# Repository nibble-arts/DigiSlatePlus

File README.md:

# DigiSlate+

The project is in an early developement state.

DigiSlate+ is inspired from the [DigiSlate](https://www.youtube.com/watch?v=TnaWQZtmPek) and the DIY timecode generator from [mitkunz](https://github.com/mitkunz/diy_timecode_generator). The aim for the DigiSlate+ is not only to be able to read and display timecode, but also to generate it itself. To make this possible, the hardware is extended by a real time clock with high running accuracy. The RTC module DS3231 with temperature-compensated quartz offers the possibility.

The DigiSlate+ has two operating states. If an external time code is fed in and the slate is switched on, it starts in read mode. The time code is read, shown on the LED display and the time in the RTC is updated. The DS3231 sends an interrupt to the controller at the beginning of each second. The offset of frames to the time code fed in is stored in the EEPROM memory in order to provide a frame-accurate time in free-running mode.

As soon as the external time code is disconnected or the slate is switched on without a time code at the input, it changes to free-running mode. It now runs automatically with the time from the RTC and the saved frame offset. The accuracy of the RTC module allows a deviation of 1 frame in 8 hours.

A socond row of 7-segment LEDs display the scene and take numbers.

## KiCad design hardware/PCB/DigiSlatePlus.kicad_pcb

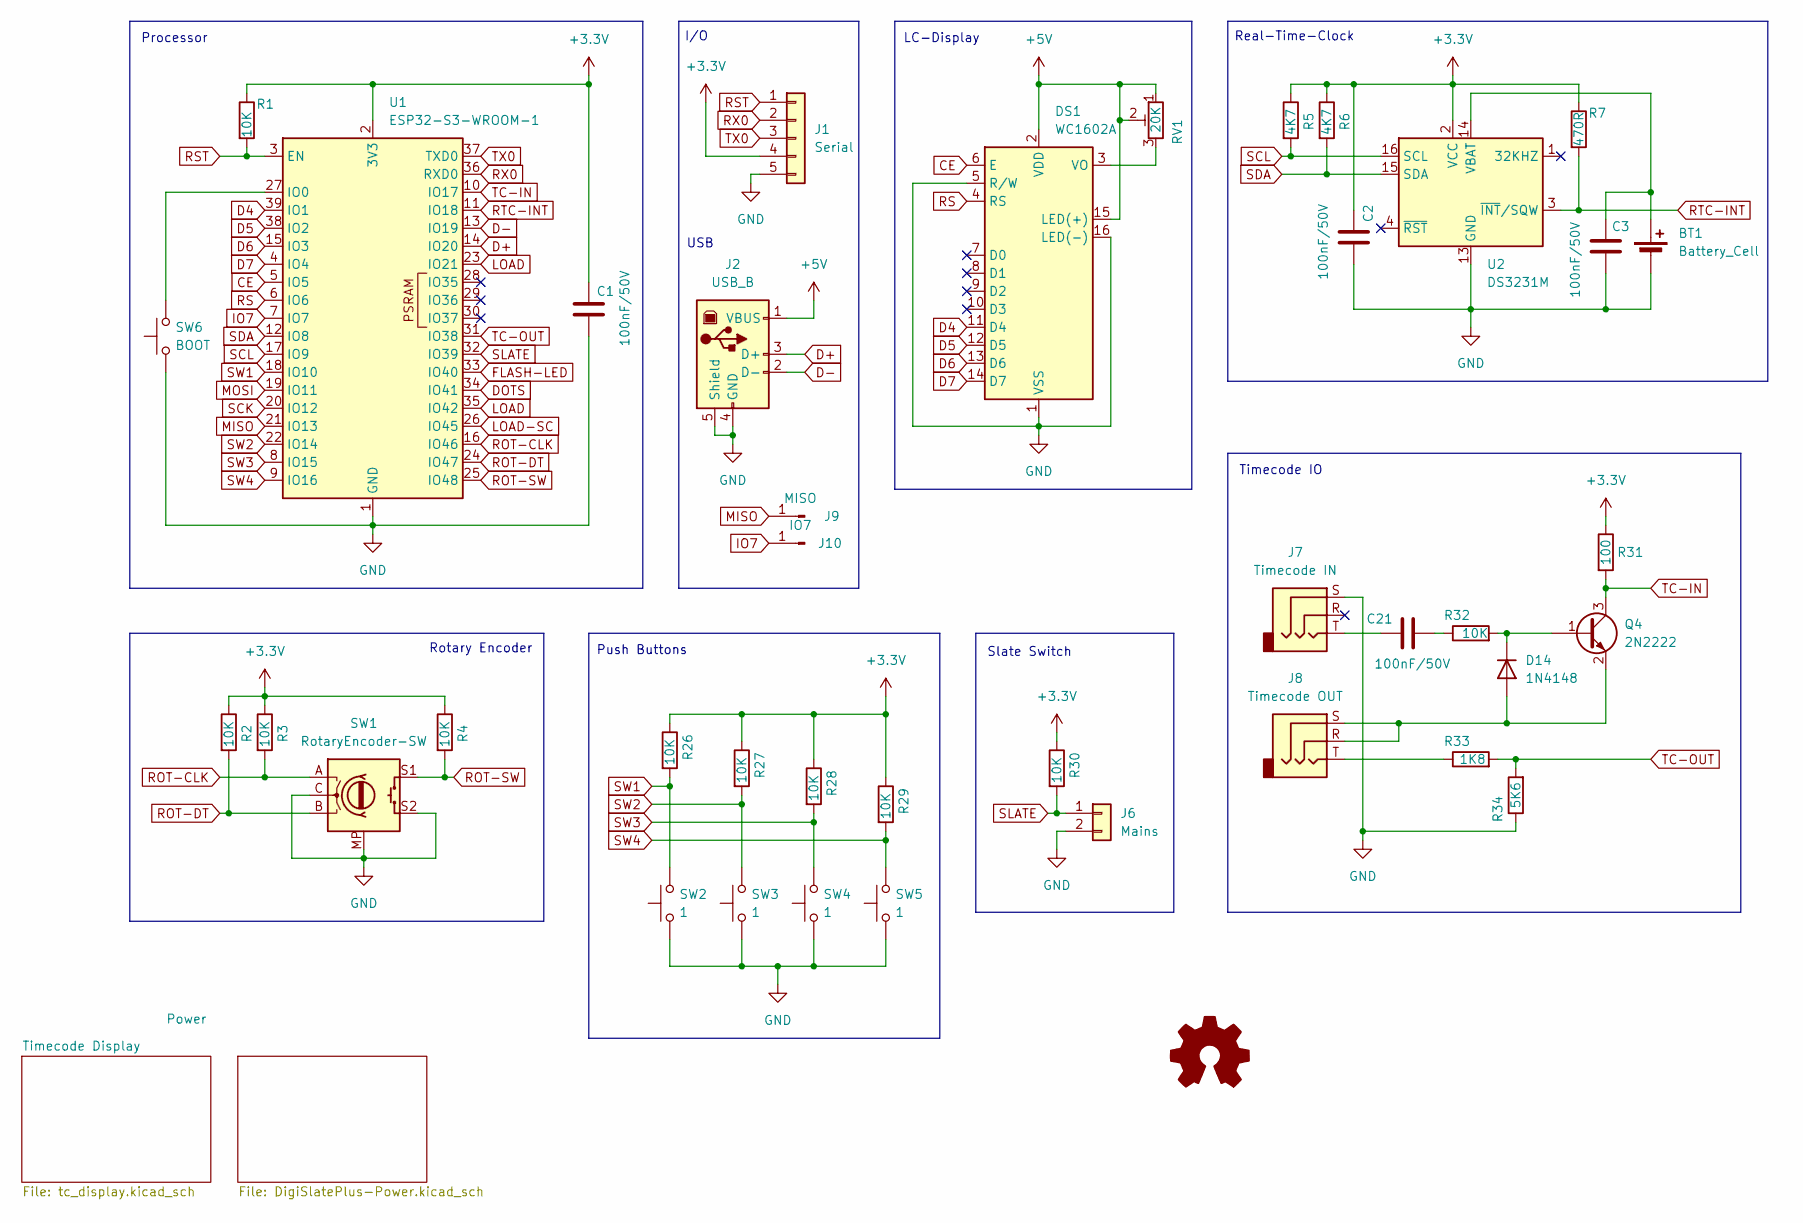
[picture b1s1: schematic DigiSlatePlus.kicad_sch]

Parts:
BT1: Battery_Cell; BatteryHolder_ComfortableElectronic_CH273-2450_1x2450
C1, C2, C3, C21: 100nF/50V; C_1206_3216Metric_Pad1.33x1.80mm_HandSolder
D14: 1N4148; D_PowerDI-123
DS1: WC1602A
J1: Serial; JST_XH_B5B-XH-AM_1x05_P2.50mm_Vertical
J2: USB_B; USB_B_Lumberg_2411_02_Horizontal
J6: Mains; JST_XH_B2B-XH-AM_1x02_P2.50mm_Vertical
J7: Timecode IN; Jack_3.5mm_CUI_SJ1-3525N_Horizontal
J8: Timecode OUT; Jack_3.5mm_CUI_SJ1-3525N_Horizontal
J9: MISO; PinHeader_1x01_P1.00mm_Vertical
J10: IO7; PinHeader_1x01_P1.00mm_Vertical
Q4: 2N2222; SOT-23
R1, R2, R3, R4, R26, R27, R28, R29, R30, R32: 10K; R_1206_3216Metric
R5, R6: 4K7; R_1206_3216Metric
R7: 470R; R_1206_3216Metric
R31: 100; R_1206_3216Metric
R33: 1K8; R_1206_3216Metric
R34: 5K6; R_1206_3216Metric
RV1: 20K; Potentiometer_Vishay_TS53YL_Vertical
SW1: RotaryEncoder-SW; RotaryEncoder_Bourns_Horizontal_PEC12R-2x17F-Sxxxx
SW2, SW3, SW4, SW5: 1; SW_PUSH-12mm
SW6: BOOT; SW_Push_SPST_NO_Alps_SKRK
U1: ESP32-S3-WROOM-1
U2: DS3231M; SOIC-16W_7.5x10.3mm_P1.27mm

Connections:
+3.3V: C1.1, C2.1, J1.4, R1.1, R2.1, R3.1, R4.1, R5.1, R6.1, R7.1, R26.1, R27.1, R28.1, R29.1, R30.1, R31.1, U1.2 (3V3), U2.2 (VCC); also elsewhere on the board
+5V: DS1.2 (VDD), DS1.15 (LED(+)), J2.1 (VBUS), RV1.1, RV1.2; also elsewhere on the board
CE: DS1.6 (E), U1.5 (IO5)
D4: DS1.11 (D4), U1.39 (IO1)
D5: DS1.12 (D5), U1.38 (IO2)
D6: DS1.13 (D6), U1.15 (IO3)
D7: DS1.14 (D7), U1.4 (IO4)
D+: J2.3 (D+), U1.14 (IO20)
D-: J2.2 (D-), U1.13 (IO19)
DOTS: U1.34 (IO41); also elsewhere on the board
FLASH-LED: U1.33 (IO40); also elsewhere on the board
GND: BT1.2 (-), C1.2, C2.2, C3.2, DS1.1 (VSS), DS1.5 (R/W), DS1.16 (LED(-)), J1.5, J2.4 (GND), J2.5 (Shield), J6.2, J7.S, R34.1, SW1.C, SW1.MP, SW1.S2, SW2.1, SW3.1, SW4.1, SW5.1, SW6.1, U1.1 (GND), U1.40 (GND), U1.41 (GND), U2.5 (GND), U2.6 (GND), U2.7 (GND), U2.8 (GND), U2.9 (GND), U2.10 (GND), U2.11 (GND), U2.12 (GND), U2.13 (GND); also elsewhere on the board
IO7: J10.1, U1.7 (IO7)
LOAD: U1.23 (IO21), U1.35 (IO42); also elsewhere on the board
LOAD-SC: U1.26 (IO45); also elsewhere on the board
MISO: J9.1, U1.21 (IO13)
MOSI: U1.19 (IO11); also elsewhere on the board
unnamed: BT1.1 (+), C3.1, U2.14 (VBAT)
unnamed: C21.1, J7.T
unnamed: C21.2, R32.1
unnamed: D14.2 (A), J8.R, J8.S, Q4.2 (E)
unnamed: D14.1 (K), Q4.1 (B), R32.2
unnamed: DS1.3 (VO), RV1.3
unnamed: J8.T, R33.1
unnamed: SW6.2, U1.27 (IO0)
ROT-CLK: R3.2, SW1.A, U1.16 (IO46)
ROT-DT: R2.2, SW1.B, U1.24 (IO47)
ROT-SW: R4.2, SW1.S1, U1.25 (IO48)
RS: DS1.4 (RS), U1.6 (IO6)
RST: J1.1, R1.2, U1.3 (EN)
RTC-INT: R7.2, U1.11 (IO18), U2.3 (~INT/SQW)
RX0: J1.2, U1.36 (RXD0)
SCK: U1.20 (IO12); also elsewhere on the board
SCL: R5.2, U1.17 (IO9), U2.16 (SCL)
SDA: R6.2, U1.12 (IO8), U2.15 (SDA)
SLATE: J6.1, R30.2, U1.32 (IO39)
SW1: R26.2, SW2.2, U1.18 (IO10)
SW2: R27.2, SW3.2, U1.22 (IO14)
SW3: R28.2, SW4.2, U1.8 (IO15)
SW4: R29.2, SW5.2, U1.9 (IO16)
TC-IN: Q4.3 (C), R31.2, U1.10 (IO17)
TC-OUT: R33.2, R34.2, U1.31 (IO38)
TX0: J1.3, U1.37 (TXD0)

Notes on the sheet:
Real-Time-Clock
Push Buttons
Timecode IO
I/O
USB
Rotary Encoder
Slate Switch
LC-Display
Processor

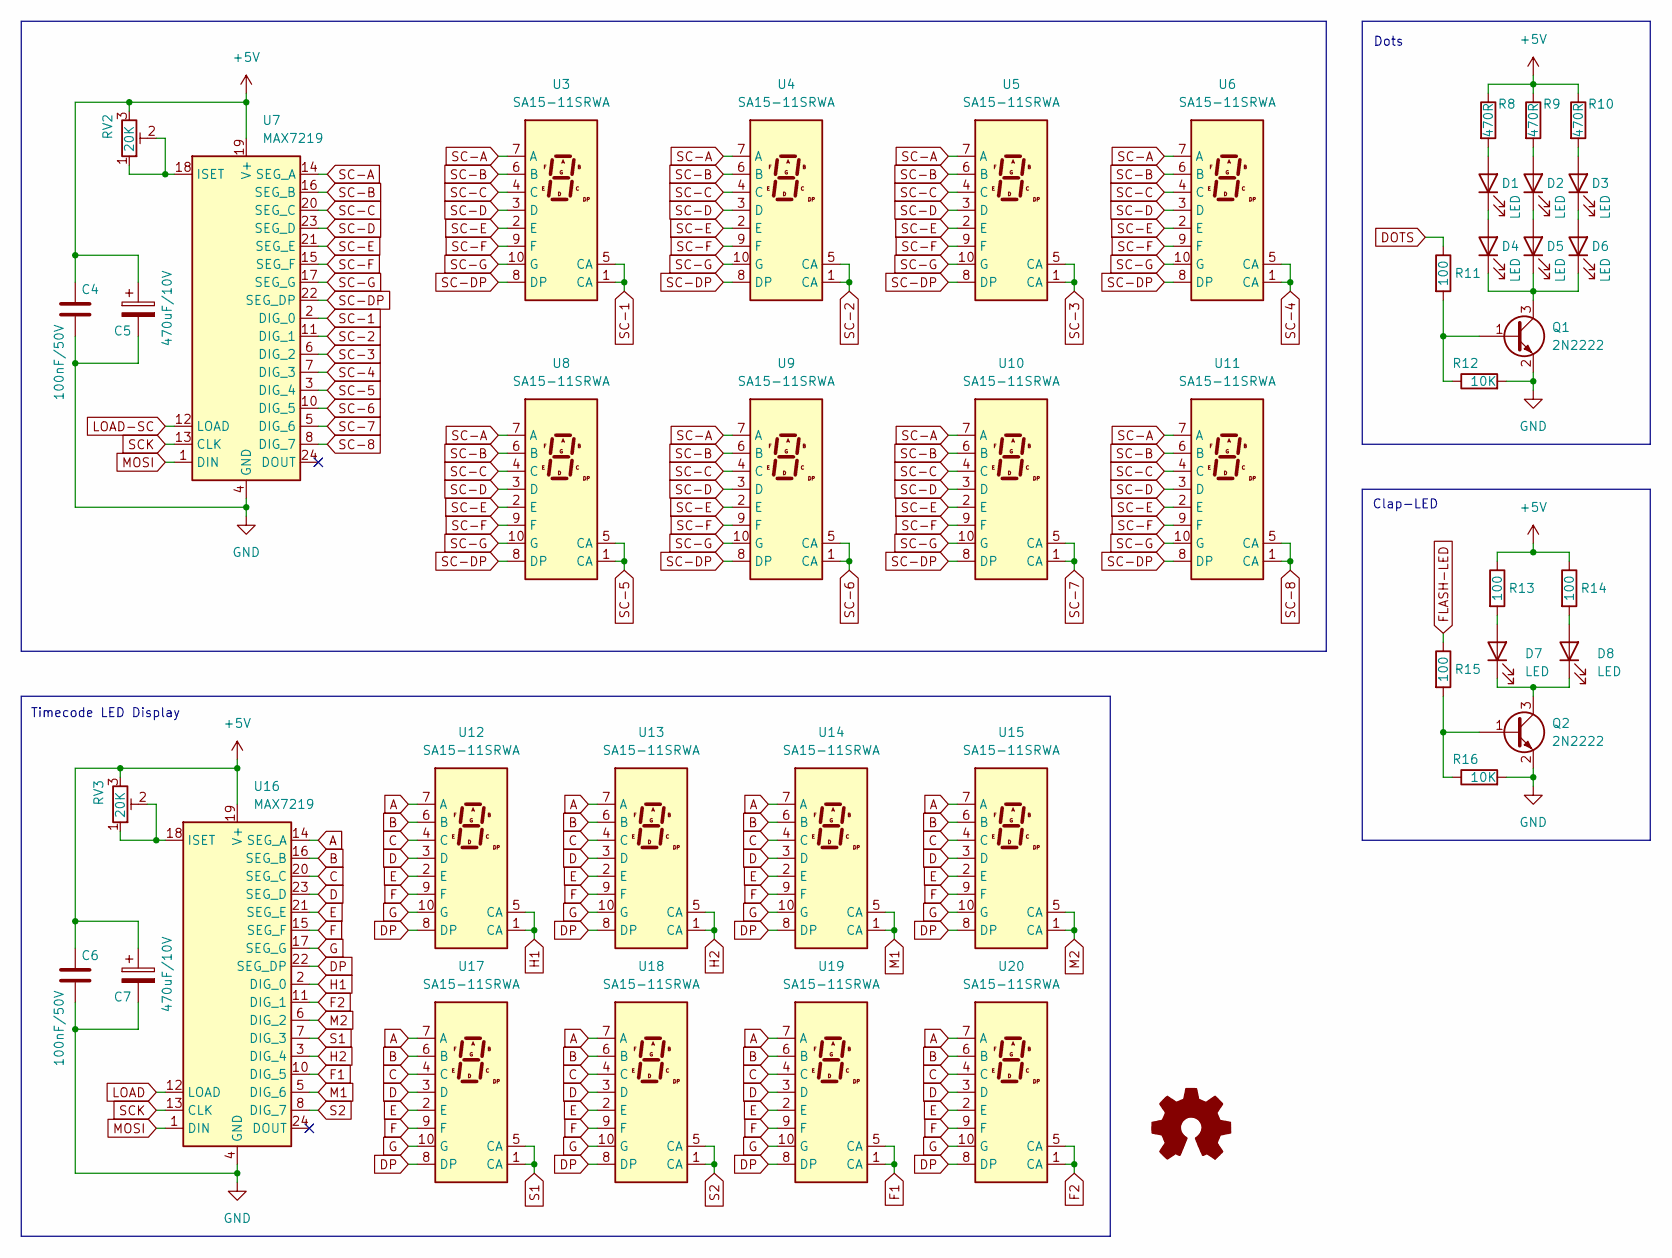
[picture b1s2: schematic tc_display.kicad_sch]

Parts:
C4, C6: 100nF/50V; C_1206_3216Metric_Pad1.33x1.80mm_HandSolder
C5, C7: 470uF/10V; CP_EIA-7343-31_Kemet-D_Pad2.25x2.55mm_HandSolder
D1, D2, D3, D4, D5, D6: LED; LED_D3.0mm_FlatTop
D7, D8: LED; LED_D10.0mm
Q1, Q2: 2N2222; SOT-23
R8, R9, R10: 470R; R_1206_3216Metric
R11, R13, R14, R15: 100; R_1206_3216Metric
R12, R16: 10K; R_1206_3216Metric
RV2, RV3: 20K; Potentiometer_Vishay_TS53YL_Vertical
U3, U4, U5, U6, U8, U9, U10, U11, U12, U13, U14, U15, U17, U18, U19, U20: SA15-11SRWA; FYS-12011A
U7, U16: MAX7219; SOIC-24W_7.5x15.4mm_P1.27mm

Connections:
+5V: C4.1, C5.1, C6.1, C7.1, R8.1, R9.1, R10.1, R13.1, R14.1, RV2.3, RV3.3, U7.19 (V+), U16.19 (V+); also elsewhere on the board
A: U12.7 (A), U13.7 (A), U14.7 (A), U15.7 (A), U16.14 (SEG_A), U17.7 (A), U18.7 (A), U19.7 (A), U20.7 (A)
B: U12.6 (B), U13.6 (B), U14.6 (B), U15.6 (B), U16.16 (SEG_B), U17.6 (B), U18.6 (B), U19.6 (B), U20.6 (B)
C: U12.4 (C), U13.4 (C), U14.4 (C), U15.4 (C), U16.20 (SEG_C), U17.4 (C), U18.4 (C), U19.4 (C), U20.4 (C)
D: U12.3 (D), U13.3 (D), U14.3 (D), U15.3 (D), U16.23 (SEG_D), U17.3 (D), U18.3 (D), U19.3 (D), U20.3 (D)
DOTS: R11.1; also elsewhere on the board
DP: U12.8 (DP), U13.8 (DP), U14.8 (DP), U15.8 (DP), U16.22 (SEG_DP), U17.8 (DP), U18.8 (DP), U19.8 (DP), U20.8 (DP)
E: U12.2 (E), U13.2 (E), U14.2 (E), U15.2 (E), U16.21 (SEG_E), U17.2 (E), U18.2 (E), U19.2 (E), U20.2 (E)
F: U12.9 (F), U13.9 (F), U14.9 (F), U15.9 (F), U16.15 (SEG_F), U17.9 (F), U18.9 (F), U19.9 (F), U20.9 (F)
F1: U16.10 (DIG_5), U19.1 (CA), U19.5 (CA)
F2: U16.11 (DIG_1), U20.1 (CA), U20.5 (CA)
FLASH-LED: R15.1; also elsewhere on the board
G: U12.10 (G), U13.10 (G), U14.10 (G), U15.10 (G), U16.17 (SEG_G), U17.10 (G), U18.10 (G), U19.10 (G), U20.10 (G)
GND: C4.2, C5.2, C6.2, C7.2, Q1.2 (E), Q2.2 (E), R12.2, R16.2, U7.4 (GND), U7.9 (GND), U16.4 (GND), U16.9 (GND); also elsewhere on the board
H1: U12.1 (CA), U12.5 (CA), U16.2 (DIG_0)
H2: U13.1 (CA), U13.5 (CA), U16.3 (DIG_4)
LOAD: U16.12 (LOAD); also elsewhere on the board
LOAD-SC: U7.12 (LOAD); also elsewhere on the board
M1: U14.1 (CA), U14.5 (CA), U16.5 (DIG_6)
M2: U15.1 (CA), U15.5 (CA), U16.6 (DIG_2)
MOSI: U7.1 (DIN), U16.1 (DIN); also elsewhere on the board
unnamed: D1.2 (A), R8.2
unnamed: D1.1 (K), D4.2 (A)
unnamed: D2.2 (A), R9.2
unnamed: D2.1 (K), D5.2 (A)
unnamed: D3.2 (A), R10.2
unnamed: D3.1 (K), D6.2 (A)
unnamed: D4.1 (K), D5.1 (K), D6.1 (K), Q1.3 (C)
unnamed: D7.2 (A), R13.2
unnamed: D7.1 (K), D8.1 (K), Q2.3 (C)
unnamed: D8.2 (A), R14.2
unnamed: Q1.1 (B), R11.2, R12.1
unnamed: Q2.1 (B), R15.2, R16.1
unnamed: RV2.1, RV2.2, U7.18 (ISET)
unnamed: RV3.1, RV3.2, U16.18 (ISET)
S1: U16.7 (DIG_3), U17.1 (CA), U17.5 (CA)
S2: U16.8 (DIG_7), U18.1 (CA), U18.5 (CA)
SC-1: U3.1 (CA), U3.5 (CA), U7.2 (DIG_0)
SC-2: U4.1 (CA), U4.5 (CA), U7.11 (DIG_1)
SC-3: U5.1 (CA), U5.5 (CA), U7.6 (DIG_2)
SC-4: U6.1 (CA), U6.5 (CA), U7.7 (DIG_3)
SC-5: U7.3 (DIG_4), U8.1 (CA), U8.5 (CA)
SC-6: U7.10 (DIG_5), U9.1 (CA), U9.5 (CA)
SC-7: U7.5 (DIG_6), U10.1 (CA), U10.5 (CA)
SC-8: U7.8 (DIG_7), U11.1 (CA), U11.5 (CA)
SC-A: U3.7 (A), U4.7 (A), U5.7 (A), U6.7 (A), U7.14 (SEG_A), U8.7 (A), U9.7 (A), U10.7 (A), U11.7 (A)
SC-B: U3.6 (B), U4.6 (B), U5.6 (B), U6.6 (B), U7.16 (SEG_B), U8.6 (B), U9.6 (B), U10.6 (B), U11.6 (B)
SC-C: U3.4 (C), U4.4 (C), U5.4 (C), U6.4 (C), U7.20 (SEG_C), U8.4 (C), U9.4 (C), U10.4 (C), U11.4 (C)
SC-D: U3.3 (D), U4.3 (D), U5.3 (D), U6.3 (D), U7.23 (SEG_D), U8.3 (D), U9.3 (D), U10.3 (D), U11.3 (D)
SC-DP: U3.8 (DP), U4.8 (DP), U5.8 (DP), U6.8 (DP), U7.22 (SEG_DP), U8.8 (DP), U9.8 (DP), U10.8 (DP), U11.8 (DP)
SC-E: U3.2 (E), U4.2 (E), U5.2 (E), U6.2 (E), U7.21 (SEG_E), U8.2 (E), U9.2 (E), U10.2 (E), U11.2 (E)
SC-F: U3.9 (F), U4.9 (F), U5.9 (F), U6.9 (F), U7.15 (SEG_F), U8.9 (F), U9.9 (F), U10.9 (F), U11.9 (F)
SC-G: U3.10 (G), U4.10 (G), U5.10 (G), U6.10 (G), U7.17 (SEG_G), U8.10 (G), U9.10 (G), U10.10 (G), U11.10 (G)
SCK: U7.13 (CLK), U16.13 (CLK); also elsewhere on the board

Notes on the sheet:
Timecode LED Display
Dots
Clap-LED

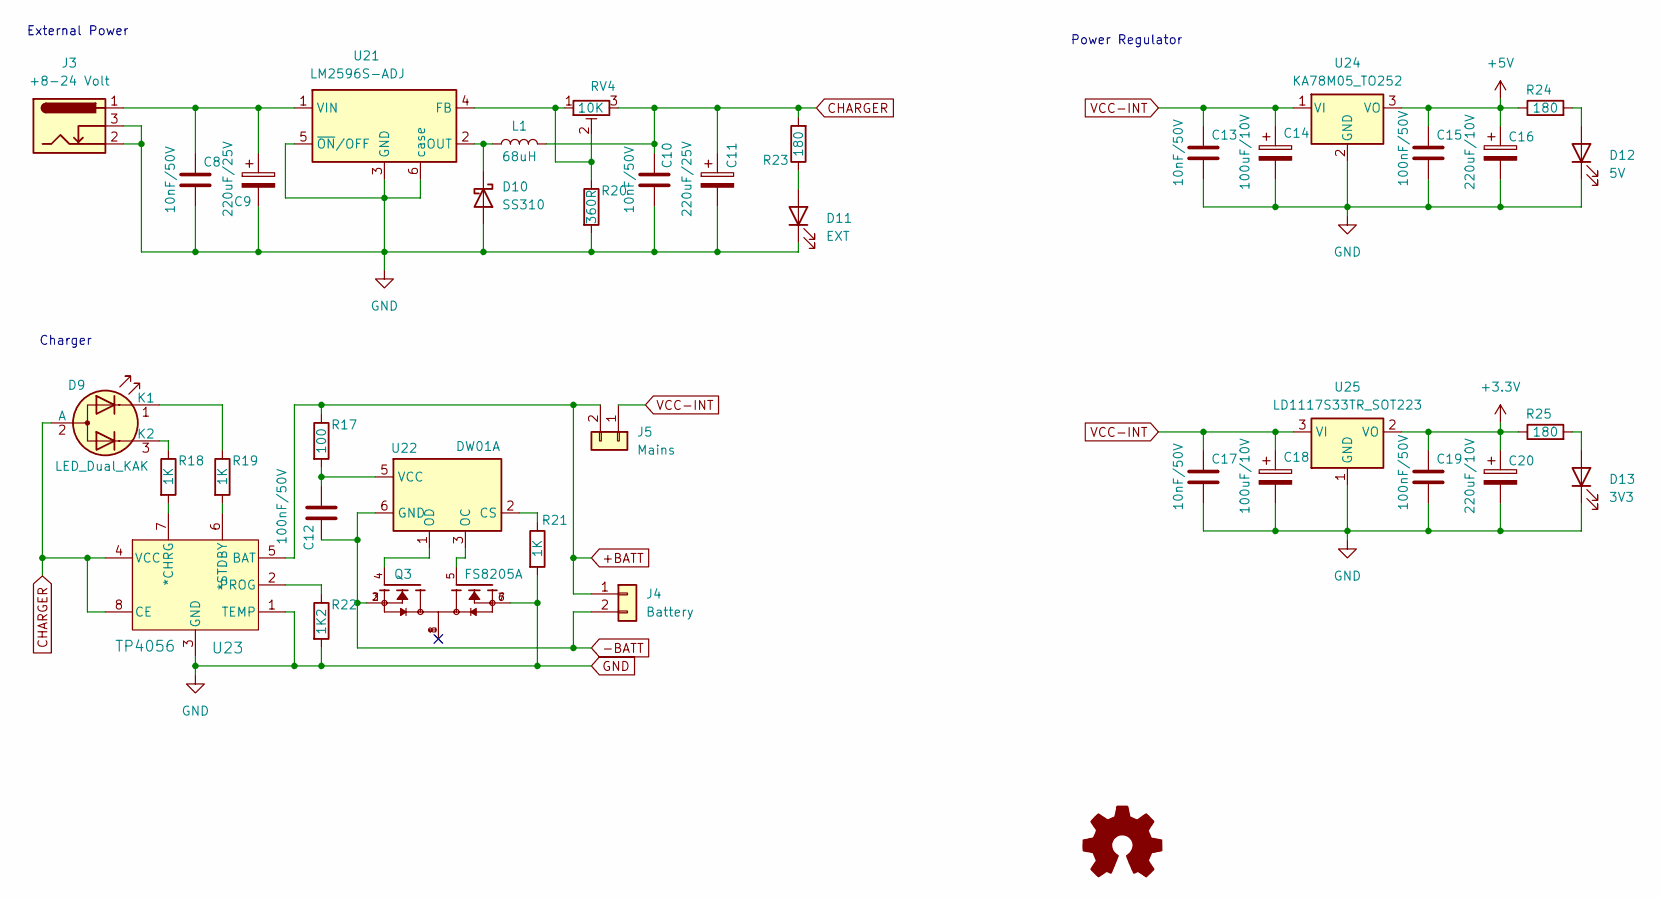
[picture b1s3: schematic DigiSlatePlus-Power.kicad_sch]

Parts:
C8, C10, C13, C17: 10nF/50V; C_1206_3216Metric_Pad1.33x1.80mm_HandSolder
C9, C11: 220uF/25V; CP_EIA-7343-31_Kemet-D_Pad2.25x2.55mm_HandSolder
C12, C15, C19: 100nF/50V; C_1206_3216Metric_Pad1.33x1.80mm_HandSolder
C14, C18: 100uF/10V; CP_EIA-7343-31_Kemet-D_Pad2.25x2.55mm_HandSolder
C16, C20: 220uF/10V; CP_EIA-7343-31_Kemet-D_Pad2.25x2.55mm_HandSolder
D9: LED_Dual_KAK; LED_D3.0mm-3
D10: SS310; D_SMA
D11: EXT; LED_D3.0mm
D12: 5V; LED_0603_1608Metric
D13: 3V3; LED_0603_1608Metric
J3: +8-24 Volt; BarrelJack_GCT_DCJ200-10-A_Horizontal
J4: Battery; JST_XH_B2B-XH-AM_1x02_P2.50mm_Vertical
J5: Mains; JST_XH_B2B-XH-AM_1x02_P2.50mm_Vertical
L1: 68uH; L_7.3x7.3_H3.5
Q3: FS8205A; TSSOP-8_3x3mm_P0.65mm; PARTREV 1.7
R17: 100; R_1206_3216Metric
R18, R19, R21: 1K; R_0805_2012Metric_Pad1.20x1.40mm_HandSolder
R20: 360R; R_1206_3216Metric
R22: 1K2; R_0805_2012Metric_Pad1.20x1.40mm_HandSolder
R23, R24, R25: 180; R_0805_2012Metric_Pad1.20x1.40mm_HandSolder
RV4: 10K; Potentiometer_Bourns_3296W_Vertical
U21: LM2596S-ADJ; TO-263-5_TabPin6
U22: DW01A; SOT-23-6
U23: TP4056; TP4056-42-ESOP8_TPW
U24: KA78M05_TO252; TO-252-2
U25: LD1117S33TR_SOT223; SOT-223-3_TabPin2

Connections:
+3.3V: C19.1, C20.1, R25.1, U25.2 (VO); also elsewhere on the board
+5V: C15.1, C16.1, R24.1, U24.3 (VO); also elsewhere on the board
+BATT: J4.1, J5.2, R17.1, U23.5 (BAT)
-BATT: C12.1, J4.2, Q3.2, Q3.3, U22.6 (GND)
CHARGER: C10.1, C11.1, D9.2 (A), L1.2, R23.2, RV4.3, U23.4 (VCC), U23.8 (CE)
GND: C8.2, C9.2, C10.2, C11.2, C13.2, C14.2, C15.2, C16.2, C17.2, C18.2, C19.2, C20.2, D10.2 (A), D11.1 (K), D12.1 (K), D13.1 (K), J3.2, J3.3, Q3.6, Q3.7, R20.2, R21.2, R22.2, U21.3 (GND), U21.5 (~ON/OFF), U21.6 (case), U23.1 (TEMP), U23.3 (GND), U24.2 (GND), U25.1 (GND); also elsewhere on the board
unnamed: D9.1 (K1), R19.1
unnamed: D9.3 (K2), R18.1
unnamed: D10.1 (K), L1.1, U21.2 (OUT)
unnamed: D11.2 (A), R23.1
unnamed: D12.2 (A), R24.2
unnamed: D13.2 (A), R25.2
unnamed: R20.1, RV4.1, RV4.2, U21.4 (FB)
unnamed: C8.1, C9.1, J3.1, U21.1 (VIN)
unnamed: R21.1, U22.2 (CS)
unnamed: Q3.5, U22.3 (OC)
unnamed: Q3.4, U22.1 (OD)
unnamed: C12.2, R17.2, U22.5 (VCC)
unnamed: R18.2, U23.7 (*CHRG)
unnamed: R19.2, U23.6 (*STDBY)
unnamed: R22.1, U23.2 (PROG)
VCC-INT: C13.1, C14.1, C17.1, C18.1, J5.1, U24.1 (VI), U25.3 (VI)

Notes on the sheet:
Power Regulator
External Power
Charger

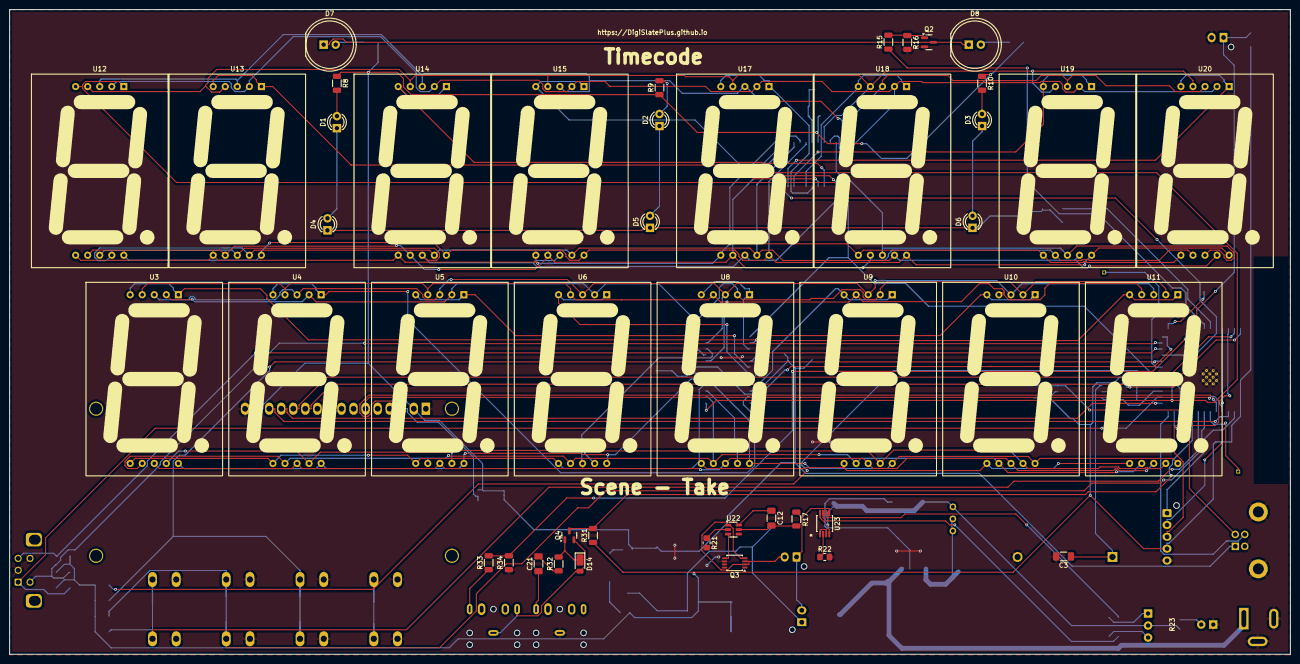
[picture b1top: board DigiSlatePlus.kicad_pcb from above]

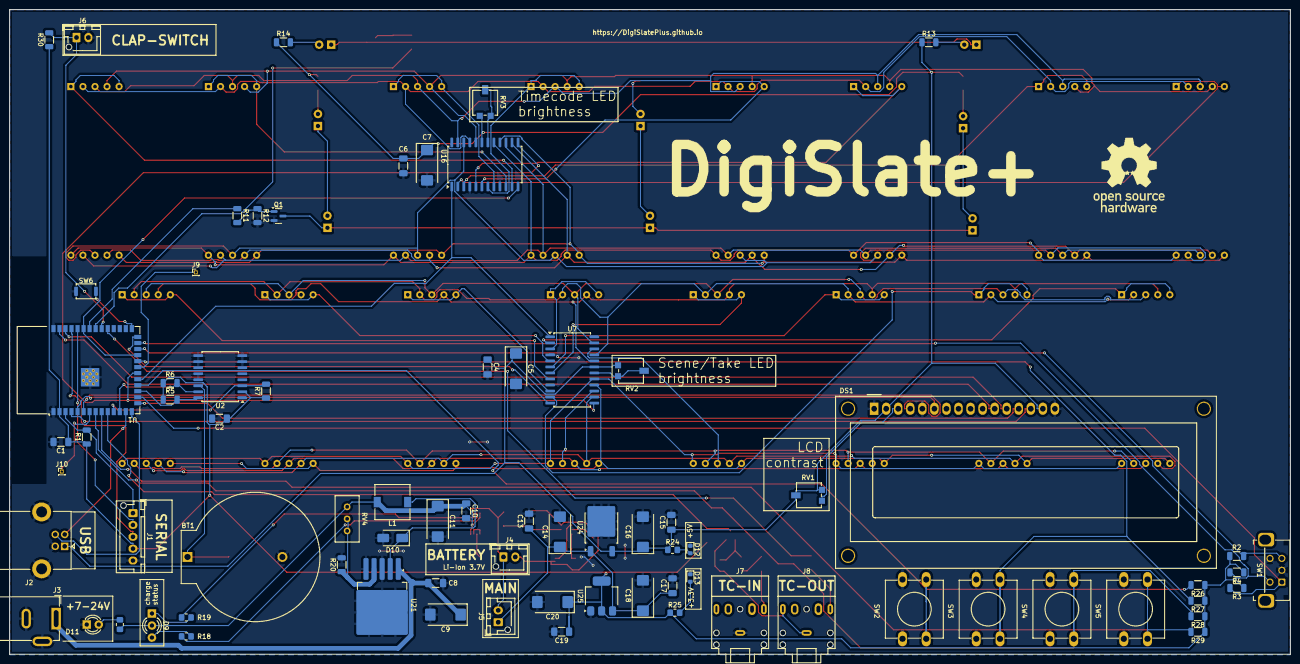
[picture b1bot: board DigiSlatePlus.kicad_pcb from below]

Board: 2 copper layers, 270.0 x 135.9 mm, 121 parts (76 on the bottom side), 108 nets.

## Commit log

2024-08-29 open source hardware icons
2024-08-29 gitignore added
